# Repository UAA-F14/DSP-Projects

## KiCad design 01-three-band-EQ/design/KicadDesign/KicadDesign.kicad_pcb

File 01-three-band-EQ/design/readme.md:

# LogFile
# 10 - 6 -26

## Fixed
- Remove Bridges
- Fix OUT_LP -> OUT_HP
- Inverted footprints of Terminals
## To fix
- Replace with the actual footprints
- Add ground plane
- Add Printed Files

# 10 - 7 - 26

## Fixed
- Add ground plane
- Replace with the actual footprints

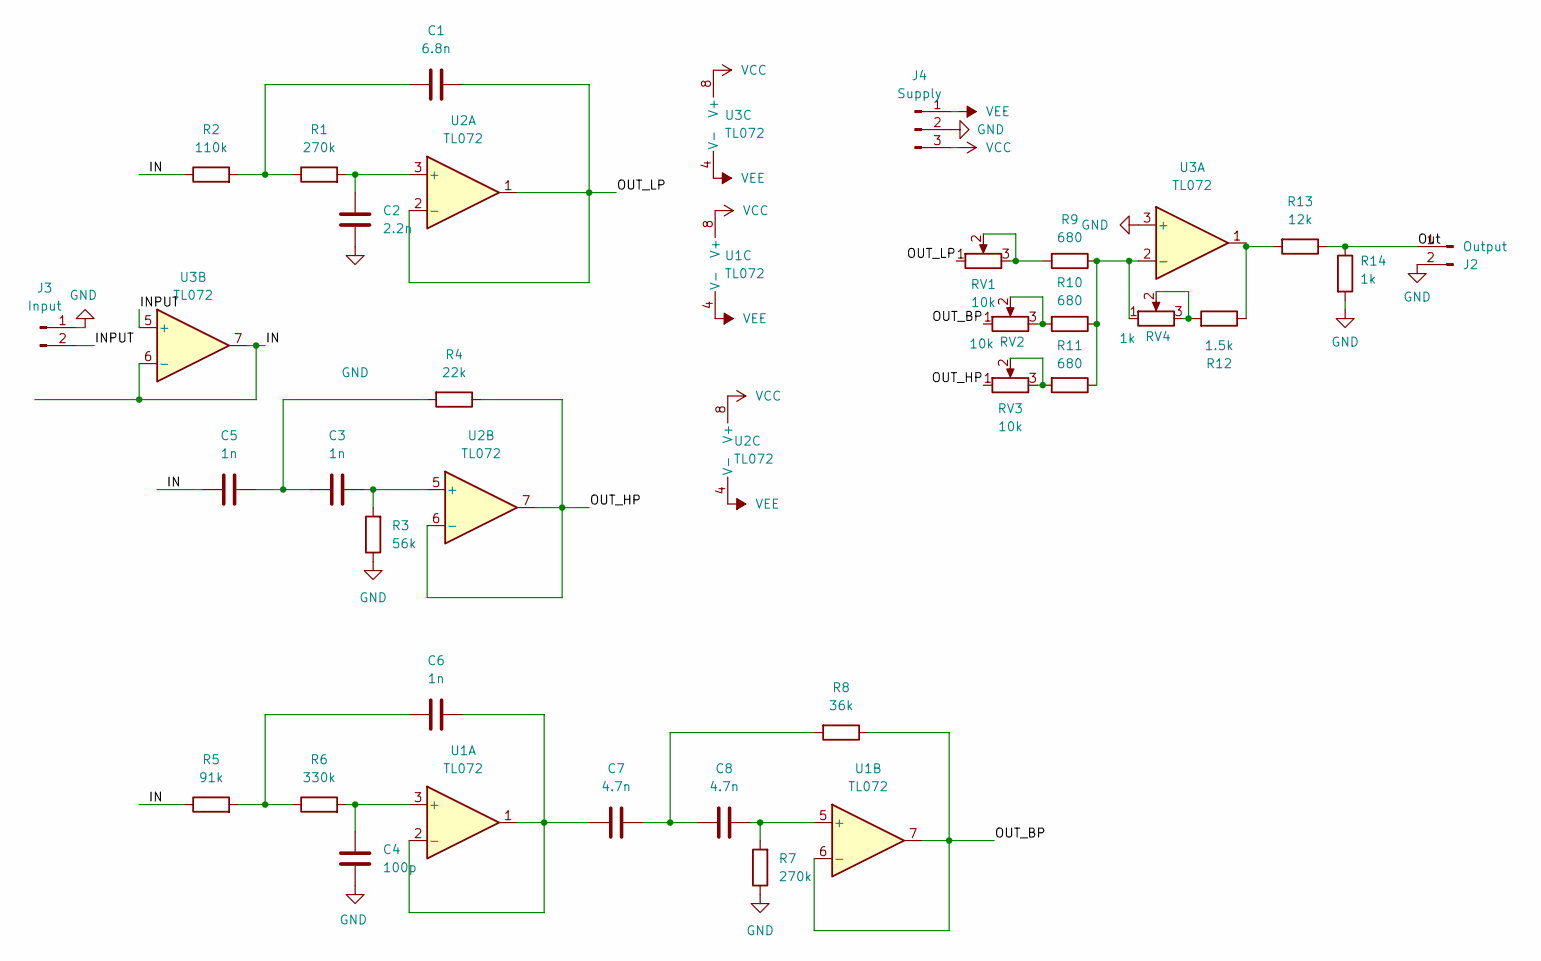
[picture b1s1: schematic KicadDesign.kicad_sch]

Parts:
C1: 6.8n; C_Disc_D5.0mm_W2.5mm_P5.00mm
C2: 2.2n; C_Disc_D5.0mm_W2.5mm_P5.00mm
C3, C6: 1n; C_Disc_D5.0mm_W2.5mm_P5.00mm
C4: 100p; C_Disc_D5.0mm_W2.5mm_P5.00mm
C5: 1n; C_Disc_D8.0mm_W5.0mm_P7.50mm
C7, C8: 4.7n; C_Disc_D5.0mm_W2.5mm_P5.00mm
J2: Output; TerminalBlock_MaiXu_MX126-5.0-02P_1x02_P5.00mm
J3: Input; TerminalBlock_MaiXu_MX126-5.0-02P_1x02_P5.00mm
J4: Supply; TerminalBlock_MaiXu_MX126-5.0-03P_1x03_P5.00mm
R1: 270k; R_Axial_DIN0207_L6.3mm_D2.5mm_P10.16mm_Horizontal
R2: 110k; R_Axial_DIN0411_L9.9mm_D3.6mm_P5.08mm_Vertical
R3: 56k; R_Axial_DIN0207_L6.3mm_D2.5mm_P10.16mm_Horizontal
R4: 22k; R_Axial_DIN0411_L9.9mm_D3.6mm_P5.08mm_Vertical
R5: 91k; R_Axial_DIN0411_L9.9mm_D3.6mm_P5.08mm_Vertical
R6: 330k; R_Axial_DIN0411_L9.9mm_D3.6mm_P5.08mm_Vertical
R7: 270k; R_Axial_DIN0411_L9.9mm_D3.6mm_P5.08mm_Vertical
R8: 36k; R_Axial_DIN0411_L9.9mm_D3.6mm_P5.08mm_Vertical
R9, R10, R11: 680; R_Axial_DIN0411_L9.9mm_D3.6mm_P5.08mm_Vertical
R12: 1.5k; R_Axial_DIN0411_L9.9mm_D3.6mm_P5.08mm_Vertical
R13: 12k; R_Axial_DIN0411_L9.9mm_D3.6mm_P5.08mm_Vertical
R14: 1k; R_Axial_DIN0411_L9.9mm_D3.6mm_P5.08mm_Vertical
RV1, RV2, RV3: 10k; Potentiometer_Alps_RK163_Single_Horizontal
RV4: 1k; Potentiometer_Alps_RK163_Single_Horizontal
U1, U2, U3: TL072; DIP-8_W7.62mm_LongPads

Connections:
/IN: C5.2, R2.1, R5.1, U3.6 (-), U3.7
/INPUT: J3.2, U3.5 (+)
/OUT_BP: R8.1, RV2.1, U1.6 (-), U1.7
/OUT_HP: R4.1, RV3.1, U2.6 (-), U2.7
/OUT_LP: C1.2, RV1.1, U2.1, U2.2 (-)
/Out: J2.1, R13.1, R14.1
GND: C2.1, C4.1, J2.2, J3.1, J4.2, R3.1, R7.1, R14.2, U3.3 (+)
unnamed: C1.1, R1.1, R2.2
unnamed: C3.2, C5.1, R4.2
unnamed: C6.1, R5.2, R6.1
unnamed: C7.1, C8.2, R8.2
unnamed: R9.2, RV1.2, RV1.3
unnamed: R10.2, RV2.2, RV2.3
unnamed: R11.2, RV3.2, RV3.3
unnamed: R12.1, R13.2, U3.1
unnamed: R12.2, RV4.2, RV4.3
unnamed: C4.2, R6.2, U1.3 (+)
unnamed: C6.2, C7.2, U1.1, U1.2 (-)
unnamed: C8.1, R7.2, U1.5 (+)
unnamed: C2.2, R1.2, U2.3 (+)
unnamed: C3.1, R3.2, U2.5 (+)
unnamed: R9.1, R10.1, R11.1, RV4.1, U3.2 (-)
VCC: J4.3, U1.8 (V+), U2.8 (V+), U3.8 (V+)
VEE: J4.1, U1.4 (V-), U2.4 (V-), U3.4 (V-)

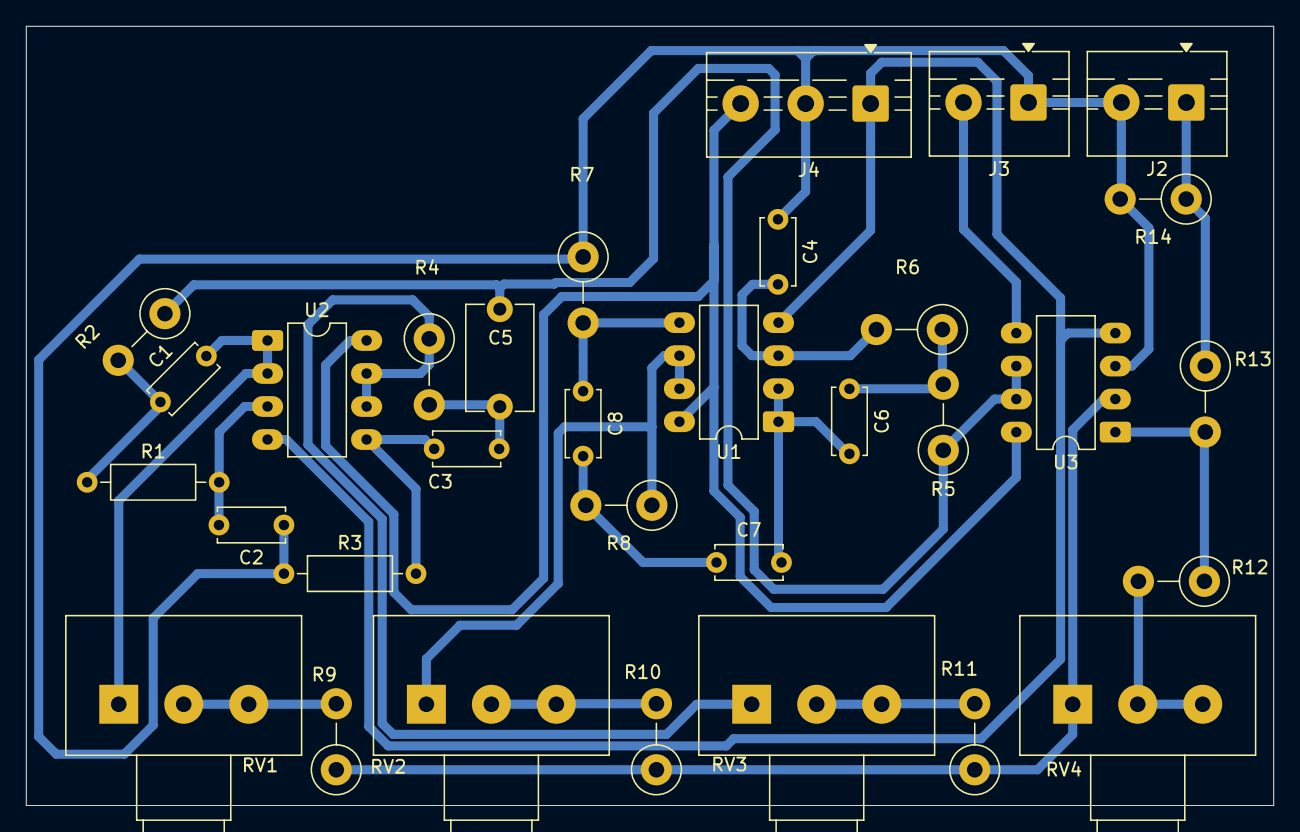
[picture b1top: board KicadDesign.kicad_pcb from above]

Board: 2 copper layers, 96.0 x 59.9 mm, 32 parts (0 on the bottom side), 24 nets.
